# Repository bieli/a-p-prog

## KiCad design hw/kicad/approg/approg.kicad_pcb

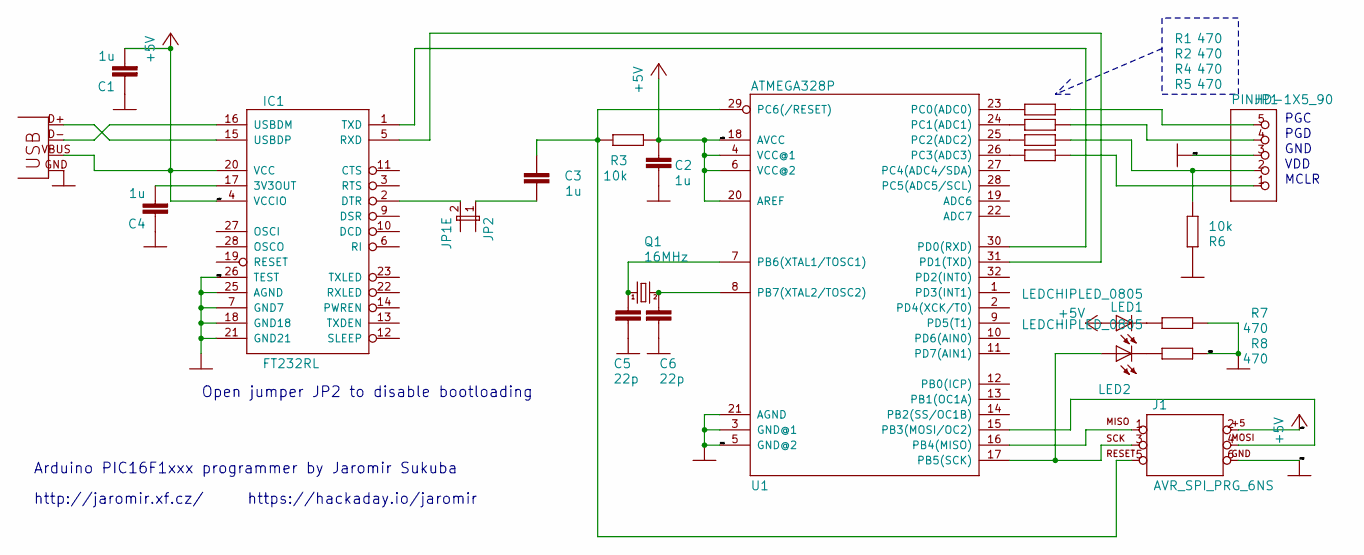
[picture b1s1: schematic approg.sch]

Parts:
C1, C2, C3, C4: 1u; R0805
C5, C6: 22p; R0805
IC1: FT232RL; SSOP28DB
J1: AVR_SPI_PRG_6NS; 2X3-NS
JP1: PINHD-1X5_90; 1X05_90
JP2: JP1E; JP1
LED1, LED2: LEDCHIPLED_0805; CHIPLED_0805
Q1: 16MHz; HC49_S
R1, R2, R4, R5, R7, R8: 470; R0805
R3, R6: 10k; R0805
U1: ATMEGA328P; TQFP32-08
X1: USB-MICROB

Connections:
+5V: C1.2, C2.1, IC1.4 (VCCIO), IC1.20 (VCC), J1.2, LED1.A, R3.1, U1.4 (VCC@1), U1.6 (VCC@2), U1.18 (AVCC), U1.20 (AREF), X1.VBUS
GND: C1.1, C2.2, C4.1, C5.2, C6.2, IC1.7 (GND7), IC1.18 (GND18), IC1.21 (GND21), IC1.25 (AGND), IC1.26 (TEST), J1.6, JP1.3, R6.2, R7.1, R8.1, U1.3 (GND@1), U1.5 (GND@2), U1.21 (AGND), X1.GND
unnamed: C3.1, J1.5, R3.2, U1.29 (PC6(/RESET))
unnamed: C3.2, JP2.1
unnamed: C4.2, IC1.17 (3V3OUT)
unnamed: C5.1, Q1.1, U1.7 (PB6(XTAL1/TOSC1))
unnamed: C6.1, Q1.2, U1.8 (PB7(XTAL2/TOSC2))
unnamed: IC1.1 (TXD), U1.30 (PD0(RXD))
unnamed: IC1.2 (DTR), JP2.2
unnamed: IC1.5 (RXD), U1.31 (PD1(TXD))
unnamed: IC1.15 (USBDP), X1.D+
unnamed: IC1.16 (USBDM), X1.D-
unnamed: J1.1, U1.16 (PB4(MISO))
unnamed: J1.3, LED2.A, U1.17 (PB5(SCK))
unnamed: J1.4, U1.15 (PB3(MOSI/OC2))
unnamed: JP1.1, R5.1
unnamed: JP1.2, R4.1, R6.1
unnamed: JP1.4, R2.1
unnamed: JP1.5, R1.1
unnamed: LED1.C, R7.2
unnamed: LED2.C, R8.2
unnamed: R1.2, U1.23 (PC0(ADC0))
unnamed: R2.2, U1.24 (PC1(ADC1))
unnamed: R4.2, U1.25 (PC2(ADC2))
unnamed: R5.2, U1.26 (PC3(ADC3))

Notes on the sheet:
MCLR
VDD
GND
PGD
PGC
Open jumper JP2 to disable bootloading
Arduino PIC16F1xxx programmer by Jaromir Sukuba
http://jaromir.xf.cz/
https://hackaday.io/jaromir

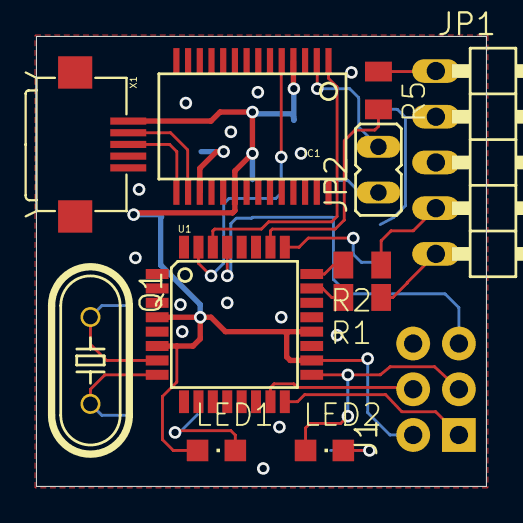
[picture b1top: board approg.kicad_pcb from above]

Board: 2 copper layers, 25.0 x 25.0 mm, 23 parts (0 on the bottom side), 25 nets.

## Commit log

2023-03-18 KiCad 5.1 hardware schematic and PCB design (converted from Eagle 6.6)
